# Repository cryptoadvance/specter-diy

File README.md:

# Specter-DIY

    "Cypherpunks write code. We know that someone has to write software to defend privacy, 
    and since we can't get privacy unless we all do, we're going to write it."
    A Cypherpunk's Manifesto - Eric Hughes - 9 March 1993

    ...and Cypherpunks do build their own Bitcoin Hardware Wallets.

The idea of the project is to build a hardware wallet from off-the-shelf components.
Even though we have [an extension board](./shield) that puts everything in a nice form-factor and helps you to avoid any soldering, we will continue supporting and maintaining compatibility with standard components.

We also want to keep the project flexible such that it can work on any other set of components with minimal changes. Maybe you want to make a hardware wallet on a different architecture (RISC-V?), with an audio modem as a communication channel - you should be able to do it. It should be easy to add or change functionality of Specter and we try to abstract logical modules as much as we can.

QR codes are a default way for Specter to communicate with the host. QR codes are pretty convenient and allow the user to be in control of the data transmission - every QR code has a very limited capacity and communication happens unidirectionally. And it's airgapped - you don't need to connect the wallet to the computer at any time.

For secret storage we support agnostic mode (wallet forgets all secrets when turned off), reckless mode (stores secrets in flash of the application microcontroller) and secure element integration is coming soon.

Our main focus is multisignature setup with other hardware wallets, but wallet can also work as a single signer. We try to make it compatible with Bitcoin Core where we can - PSBT for unsigned transactions, wallet descriptors for importing/exporting multisig wallets. To communicate with Bitcoin Core easier we are also working on [Specter Desktop app](https://github.com/cryptoadvance/specter-desktop) - a small python flask server talking to your Bitcoin Core node.

Most of the firmware is written in MicroPython which makes the code easy to audit and change. We use [secp256k1](https://github.com/bitcoin-core/secp256k1) library from Bitcoin Core for elliptic curve calculations and [LVGL](https://lvgl.io/) library for GUI.

## DISCLAIMER

The project has significantly matured, to the extent that the security level of Specter-DIY is now comparable to commercial hardware wallets on the market. We implemented a secure bootloader that verifies firmware upgrades, so you can be sure that only signed firmware can be uploaded to the device after initial setup. However, unlike with commercial signing devices the bootloader has to be installed manually by the user and is not set in the factory of the device vendor. Thus, pay extra attention during the initial firmware installation and make sure you verified PGP signatures and flash the firmware from a secure computer.

If something doesn't work open an issue here or ask a question in our [Telegram group](https://t.me/+VEinVSYkW5TUl5Ai).

## Documentation

All the docs are stored in the [`docs/`](./docs) folder:

- [`shopping.md`](./docs/shopping.md) explains what to buy
- [`assembly.md`](./docs/assembly.md) shows how to put everything together.
- [`quickstart.md`](./docs/quickstart.md) guides you through the initial steps how to get firmware on the board
- [`reproducible-build.md`](./docs/reproducible-build.md) describes how to build the initial firmware and upgrade files with the same hash as in the release using Docker
- [`build.md`](./docs/build.md) describes how to build the firmware and the simulator yourself
- [`security-model.md`](./docs/security-model.md) explains possible attack vectors and security model of the project
- [`SECURITY.md`](./SECURITY.md) describes how to report vulnerabilities (disclosure policy)
- [`development.md`](./docs/development.md) explains how to start developing on Specter
- [`simulator.md`](./docs/simulator.md) shows how to run a simulator on unix/macOS
- [`browser-simulator.md`](./docs/browser-simulator.md) explains the browser preview service and paired-fork setup
- [`communication.md`](./docs/communication.md) defines communication protocol with the host over QR codes and USB
- [`roadmap.md`](./docs/roadmap.md) explains what we need to implement before we can consider the wallet be ready to use with real funds.

Specter-Shield documentation and all the files are available in the [`shield/`](./shield) folder:

- [What it looks like](./shield/README.md)
- [How to print a 3d case](./shield/3dprinting.md)

Specter Shield-Lite documentation is available in the [`shield-lite/`](./shield-lite) folder:

- [Specter Shield-Lite overview](./shield-lite/readme.md)

Supported networks: Mainnet, Testnet, Regtest, Signet.

## Running tests

The unit test suite runs on the Unix simulator build. Install the required
system packages and then run the `make` target:

```
sudo apt-get update
sudo apt-get install libsdl2-dev libffi-dev pkg-config libreadline-dev libgmp-dev build-essential python3
make test
```

The build system will fetch the necessary submodules and compile the simulator
before executing the tests.

## USB communication on Linux

You may need to set up udev rules and add yourself to `dialout` group. Read more in [`udev`](./udev/README.md) folder.

## Video and screenshots

Check out [this video](https://www.youtube.com/watch?v=1H7FqG_FmCw) to get an idea how to assemble it and how it works.

Here is a [Gallery](./docs/pictures/gallery/README.md) with devices assembled by the community.

A few pictures of the UI:

### Wallet screens

### Key generation and recovery

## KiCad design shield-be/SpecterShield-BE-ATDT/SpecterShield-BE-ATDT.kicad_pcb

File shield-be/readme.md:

# Shield-BE (Budget Edition)
Work in Progress, currently untested.

The goal of this board is to provide the full functionality of the Specter Shield at a lower price.

The design parameters to enable this are:
*  4 layer PCB with largest dimension 10cm or less, min hole size 0.3mm (keeps cost down, $7 for 5pcbs)
*  All components on one side (keep fab costs down)
*  Generally target 0805 size components (make hand assembly accessible)
*  Prioritize JLCPCB basic parts, even if it means more parts taking up more space (again, to keeps costs down)
*  Can run off usb-c either with or without a battery. (Current full shield needed a battery to work, this board will not)
*  Powers the board directly from USBC when connected, rather than through the battery. (This adds some load constraints depending on what max current we assume for the USBC port. 1.5amp is probably reasonable for usb3 ports that supporting charging and will work for all USBC) Could add a resistor that is easily cut off to drop charge current down so that it will charge *and* run even off an older 1amp supply.
*  Switch mode power supply can deliver 1amp continuous with input from 3v-5v (so plenty of headroom for Specter)
*  For battery varients, can charge the lithium battery and has relevant indicator lights
*  Has power buttons, uses existing pwr_hold functionality and has power indicator when it's on.
*  Multiple varients of same design, one PCB and form factor. (Can have full shield, remove battery for shield core or remove all power for shield lite)
*  Battery level measurement on battery varient (Just using an onboard ADC, will require additional code, but will be straightforward)
*  Fully designed in kicad for portability and maintenance with FOSS tools
*  Reference case in freecad for portability and maintenance with FOSS tools

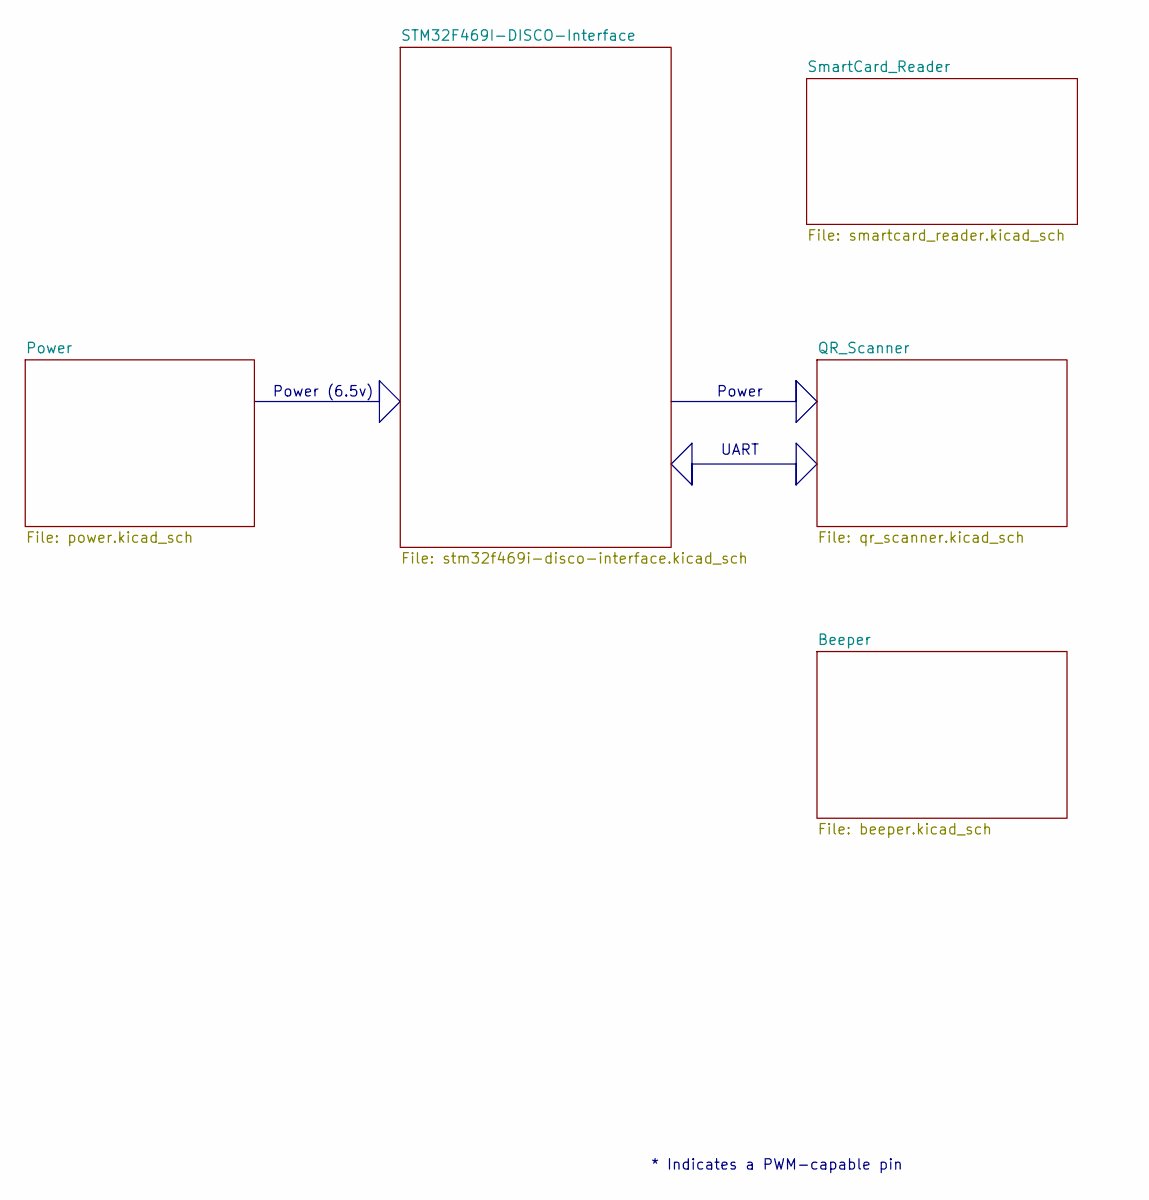
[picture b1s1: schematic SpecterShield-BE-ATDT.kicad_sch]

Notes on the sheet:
Power (6.5v)
Power
UART
* Indicates a PWM-capable pin

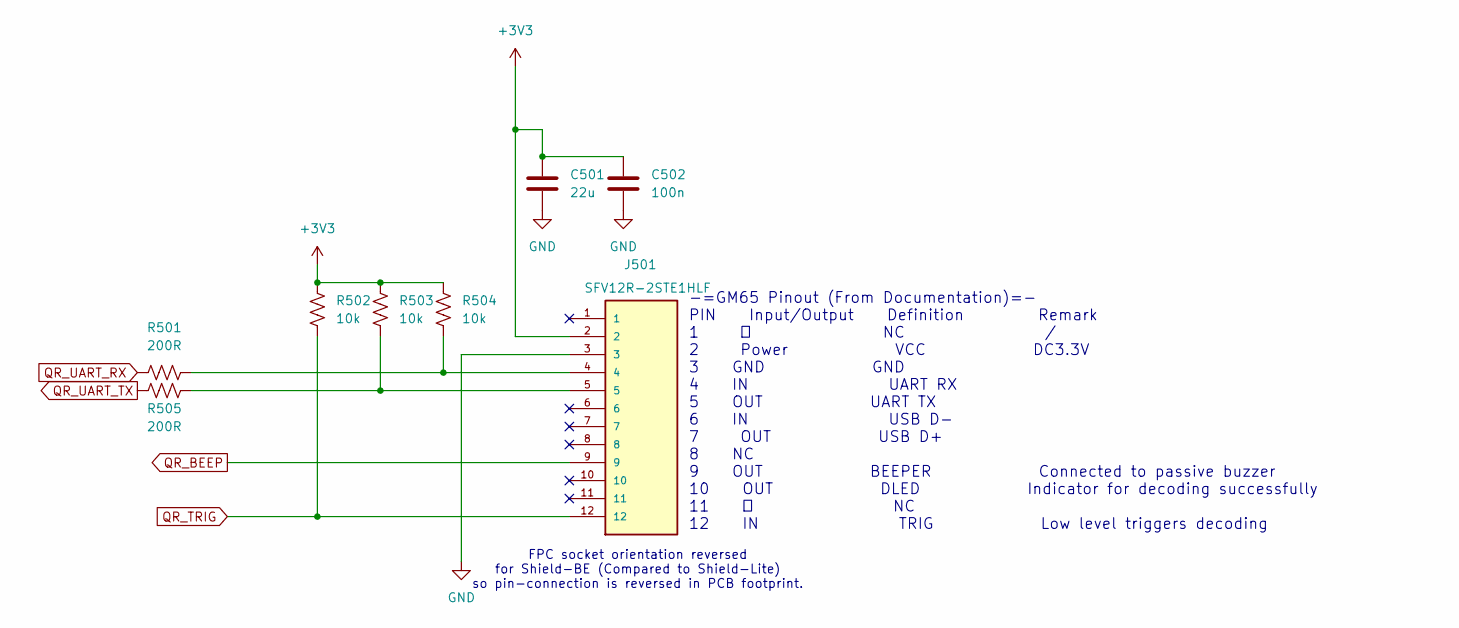
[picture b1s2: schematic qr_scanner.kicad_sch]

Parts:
C501: 22u; C_0805_2012Metric_Pad1.18x1.45mm_HandSolder; LCSC C45783
C502: 100n; C_0805_2012Metric_Pad1.18x1.45mm_HandSolder; LCSC C49678
J501: SFV12R-2STE1HLF; AMPHENOL_SFV12R-2STE1HLF_handsolder; PARTREV C; LCSC C11086
R501, R505: 200R; R_0805_2012Metric_Pad1.20x1.40mm_HandSolder; LCSC C17540
R502, R503, R504: 10k; R_0805_2012Metric_Pad1.20x1.40mm_HandSolder; LCSC C17414

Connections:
+3V3: C501.1, C502.1, J501.2, R502.1, R503.1, R504.1; also elsewhere on the board
GND: C501.2, C502.2, J501.3; also elsewhere on the board
unnamed: J501.4, R501.2, R504.2
unnamed: J501.5, R503.2, R505.2
QR_BEEP: J501.9; also elsewhere on the board
QR_TRIG: J501.12, R502.2; also elsewhere on the board
QR_UART_RX: R501.1; also elsewhere on the board
QR_UART_TX: R505.1; also elsewhere on the board

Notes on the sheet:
FPC socket orientation reversed for Shield-BE (Compared to Shield-Lite) so pin-connection is reversed in PCB footprint.
-=GM65 Pinout (From Documentation)=- PIN Input/Output Definition Remark 1 － NC / 2 Power VCC DC3.3V 3 GND GND 4 IN UART RX 5 OUT UART TX 6 IN USB D- 7 OUT USB D+ 8 NC 9 OUT BEEPER Connected to passive buzzer 10 OUT DLED Indicator for decoding successfully 11 － NC 12 IN TRIG Low level triggers decod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

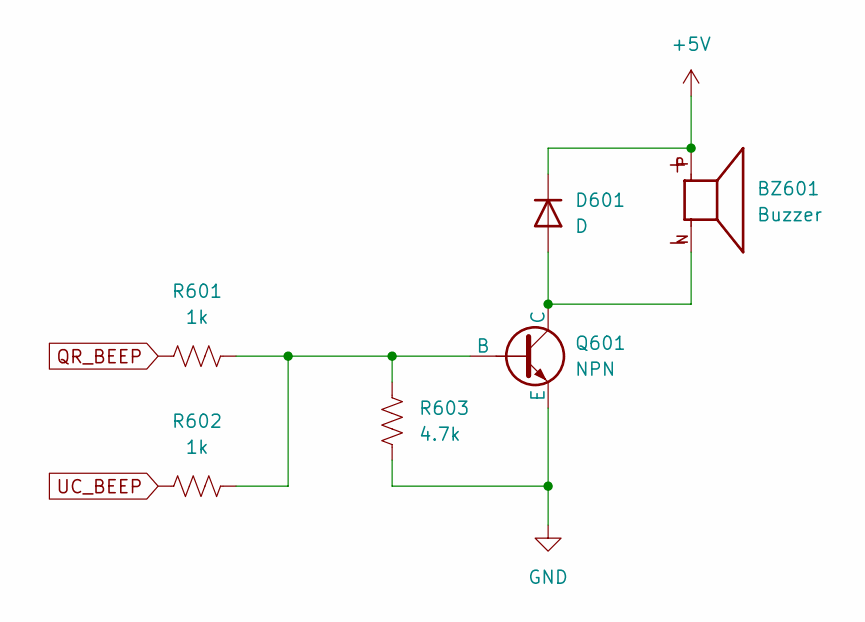
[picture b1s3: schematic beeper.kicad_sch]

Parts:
BZ601: Buzzer; XDCR_SMT-0927-S-HT-R_handsolder; PARTREV 31/03/20; LCSC C18623826
D601: D; D_SOD-123; LCSC C81598
Q601: NPN; SOT-89-3_Handsoldering; LCSC C9634
R601, R602: 1k; R_0805_2012Metric_Pad1.20x1.40mm_HandSolder; LCSC C17513
R603: 4.7k; R_0805_2012Metric_Pad1.20x1.40mm_HandSolder; LCSC C17673

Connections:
+5V: BZ601.P, D601.1 (K); also elsewhere on the board
GND: Q601.3 (E), R603.1; also elsewhere on the board
unnamed: BZ601.N, D601.2 (A), Q601.2 (C)
unnamed: Q601.1 (B), R601.2, R602.2, R603.2
QR_BEEP: R601.1; also elsewhere on the board
UC_BEEP: R602.1; also elsewhere on the board

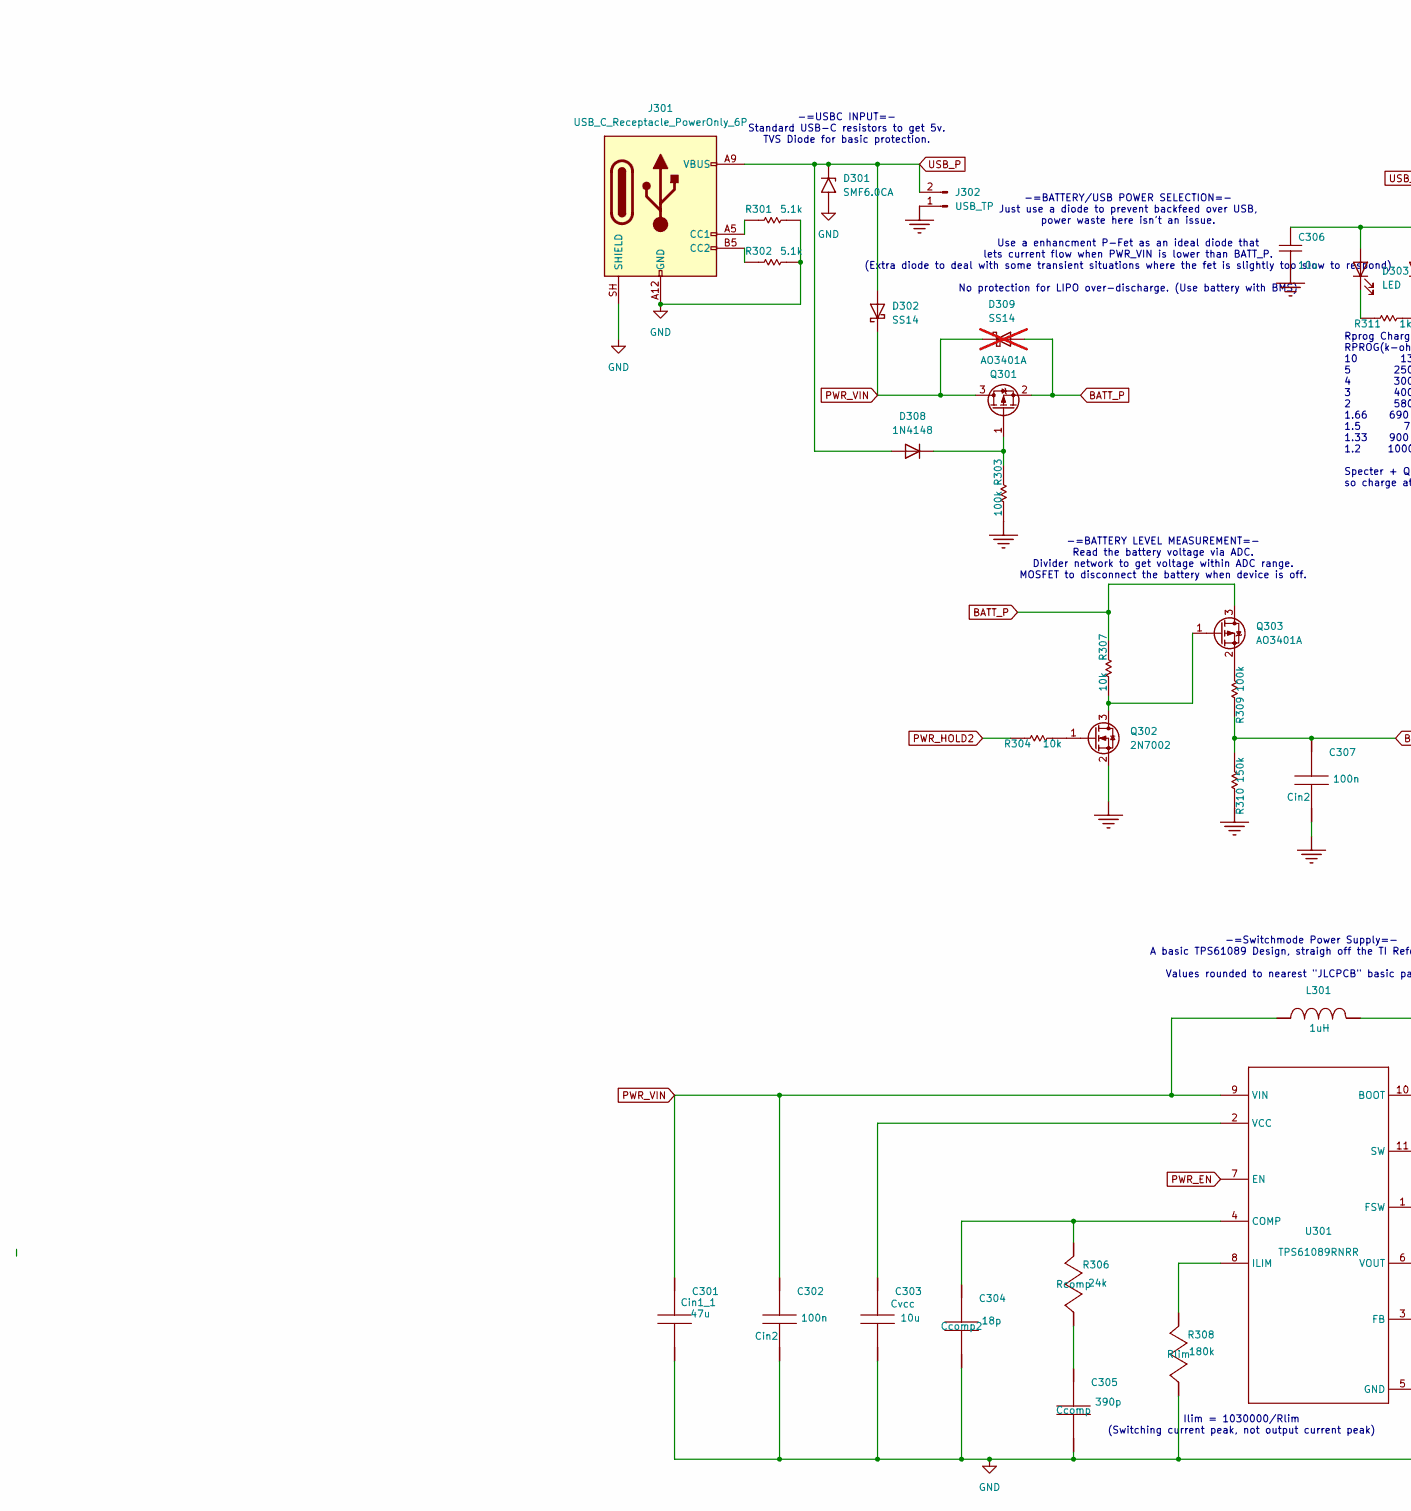
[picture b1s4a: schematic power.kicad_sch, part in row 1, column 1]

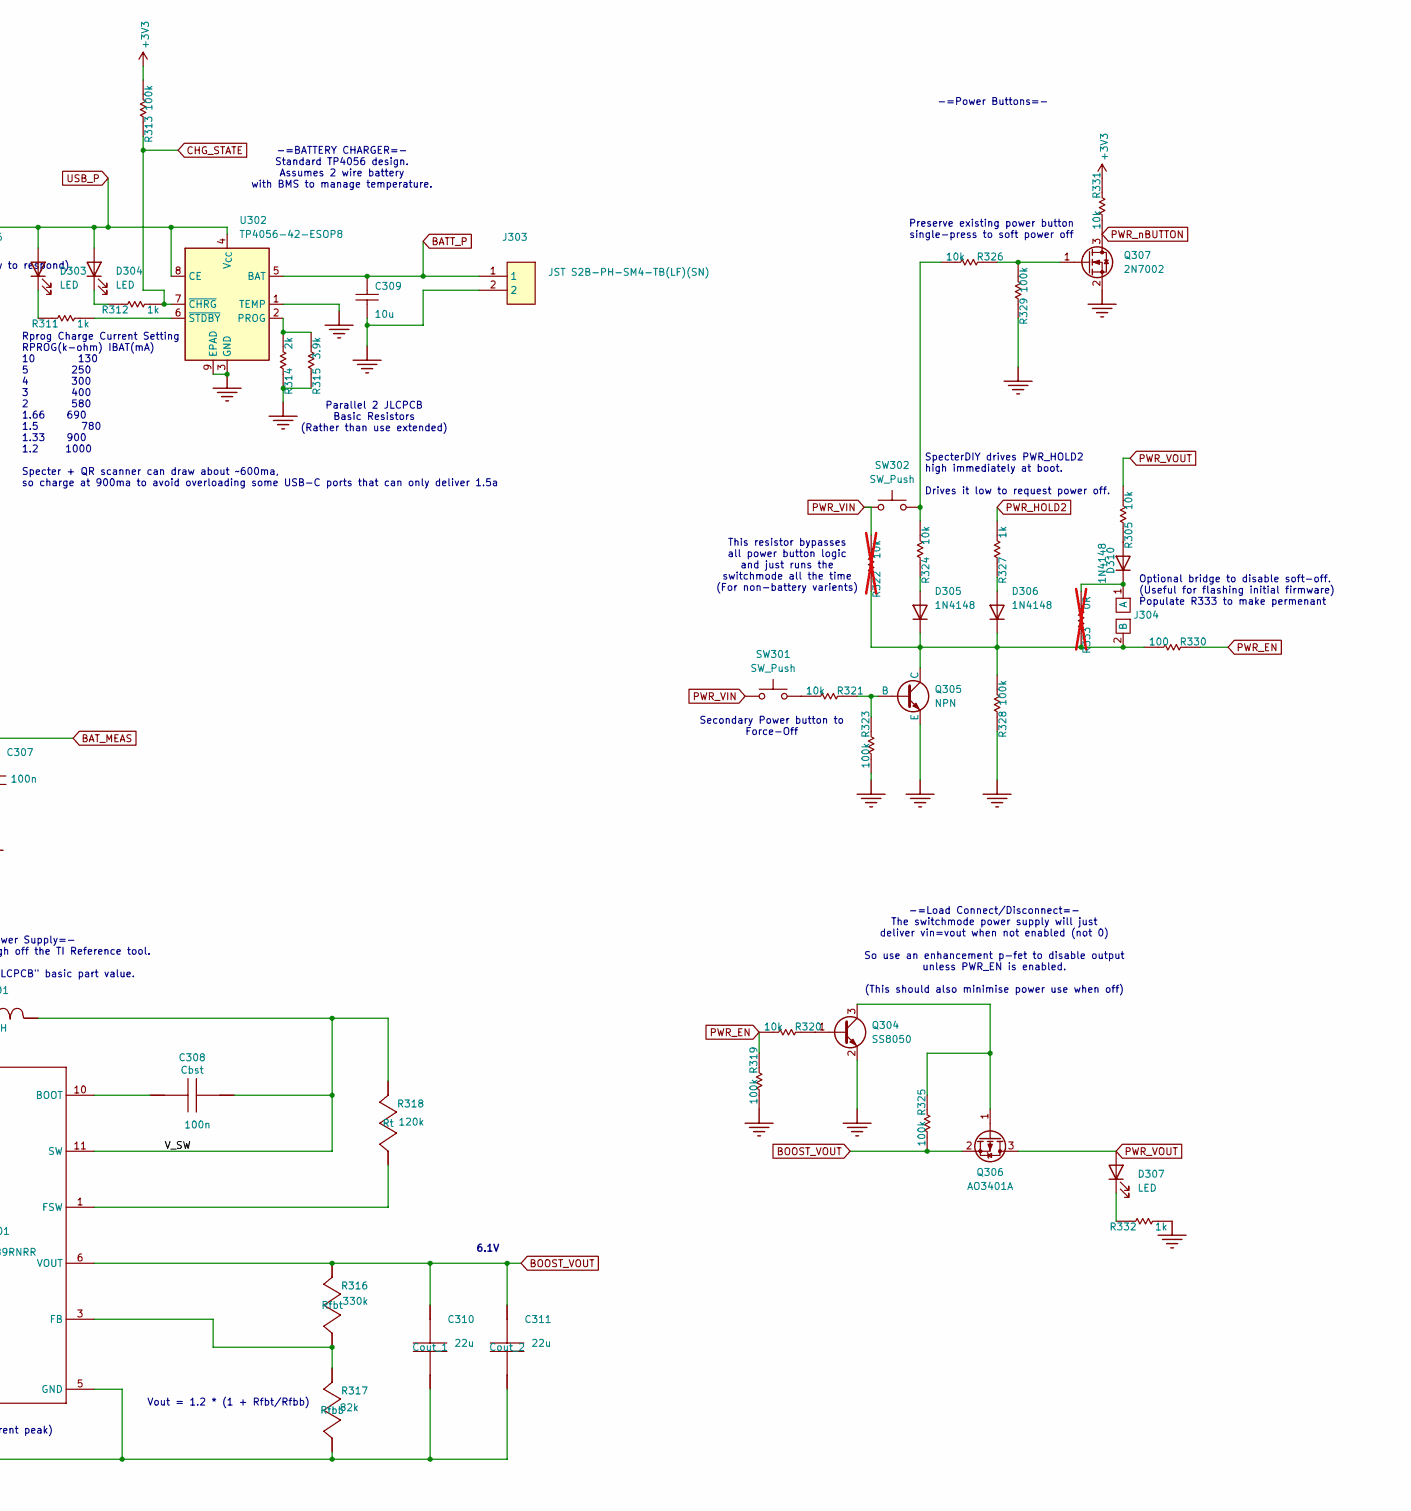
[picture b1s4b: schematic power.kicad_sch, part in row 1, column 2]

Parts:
C301: 47u; C_1206_3216Metric_Pad1.33x1.80mm_HandSolder; LCSC C96123
C302, C307, C308: 100n; C_0805_2012Metric_Pad1.18x1.45mm_HandSolder; LCSC C49678
C303: 10u; C_0805_2012Metric_Pad1.18x1.45mm_HandSolder; LCSC C15850
C304: 18p; C_0805_2012Metric_Pad1.18x1.45mm_HandSolder; LCSC C1797
C305: 390p; C_0805_2012Metric_Pad1.18x1.45mm_HandSolder; LCSC C1743
C306, C309: 10u; C_0805_2012Metric_Pad1.18x1.45mm_HandSolder; VOLTAGE RATING (DC) 50.0 V; CAPACITANCE TOLERANCE ±10%; MANUFACTURER PART NUMBER CL05B152KB5NNNC; LCSC C15850
C310, C311: 22u; C_0805_2012Metric_Pad1.18x1.45mm_HandSolder; LCSC C45783
D301: SMF6.0CA; D_SOD-123F; LCSC C2990473
D302: SS14; D_SMA; LCSC C2480
D303: LED; LED_0805_2012Metric_Pad1.15x1.40mm_HandSolder; LCSC C2296
D304: LED; LED_0805_2012Metric_Pad1.15x1.40mm_HandSolder; LCSC C84256
D305, D306, D310: 1N4148; D_SOD-323_HandSoldering; LCSC C2128
D307: LED; LED_0805_2012Metric_Pad1.15x1.40mm_HandSolder; LCSC C2297
D308: 1N4148; D_SOD-323
D309: SS14; D_SMA; LCSC C2480; not fitted
J301: USB_C_Receptacle_PowerOnly_6P; USB_C_Receptacle_HRO_TYPE-C-31-M-17; LCSC C668623
J302: USB_TP; PinHeader_1x02_P2.54mm_Vertical
J303: JST S2B-PH-SM4-TB(LF)(SN); JST_PH_S2B-PH-SM4-TB_1x02-1MP_P2.00mm_Horizontal; LCSC C295747
J304: BridgePads
L301: 1uH; L_1210_3225Metric_Pad1.42x2.65mm_HandSolder; LCSC C3002557
Q301, Q303, Q306: AO3401A; SOT-23; LCSC C15127
Q302, Q307: 2N7002; SOT-23; LCSC C8545
Q304: SS8050; SOT-23; LCSC C2150
Q305: NPN; SOT-89-3_Handsoldering; LCSC C9634
R301, R302: 5.1k; R_0805_2012Metric_Pad1.20x1.40mm_HandSolder; POWER RATING 0.0625 W; RESISTANCE TOLERANCE ±1%; MANUFACTURER PART NUMBER RC0402FR-07200RL; LCSC C27834
R303, R309, R313, R319, R323, R325, R328, R329: 100k; R_0805_2012Metric_Pad1.20x1.40mm_HandSolder; POWER RATING 0.063 W; RESISTANCE TOLERANCE ±1%; MANUFACTURER PART NUMBER RC0402FR-07120KL; LCSC C149504
R304, R305, R307, R320, R321, R324, R326, R331: 10k; R_0805_2012Metric_Pad1.20x1.40mm_HandSolder; POWER RATING 0.063 W; RESISTANCE TOLERANCE ±1%; MANUFACTURER PART NUMBER RC0402FR-07120KL; LCSC C17414
R306: 24k; R_0805_2012Metric_Pad1.20x1.40mm_HandSolder; LCSC C17575
R308: 180k; R_0805_2012Metric_Pad1.20x1.40mm_HandSolder; LCSC C17501
R310: 150k; R_0805_2012Metric_Pad1.20x1.40mm_HandSolder; POWER RATING 0.063 W; RESISTANCE TOLERANCE ±1%; MANUFACTURER PART NUMBER RC0402FR-07120KL; LCSC C17470
R311, R312, R327, R332: 1k; R_0805_2012Metric_Pad1.20x1.40mm_HandSolder; POWER RATING 0.063 W; RESISTANCE TOLERANCE ±1%; MANUFACTURER PART NUMBER RC0402FR-07120KL; LCSC C17513
R314: 2k; R_0805_2012Metric_Pad1.20x1.40mm_HandSolder; POWER RATING 0.063 W; RESISTANCE TOLERANCE ±1%; MANUFACTURER PART NUMBER RC0402FR-07120KL; LCSC C17604
R315: 3.9k; R_0805_2012Metric_Pad1.20x1.40mm_HandSolder; POWER RATING 0.063 W; RESISTANCE TOLERANCE ±1%; MANUFACTURER PART NUMBER RC0402FR-07120KL; LCSC C17614
R316: 330k; R_0805_2012Metric_Pad1.20x1.40mm_HandSolder; LCSC C23137
R317: 82k; R_0805_2012Metric_Pad1.20x1.40mm_HandSolder; LCSC C17840
R318: 120k; R_0805_2012Metric_Pad1.20x1.40mm_HandSolder; LCSC C25808
R322: 10k; R_0805_2012Metric_Pad1.20x1.40mm_HandSolder; POWER RATING 0.063 W; RESISTANCE TOLERANCE ±1%; MANUFACTURER PART NUMBER RC0402FR-07120KL; LCSC C17414; not fitted
R330: 100; R_0805_2012Metric_Pad1.20x1.40mm_HandSolder; POWER RATING 0.063 W; RESISTANCE TOLERANCE ±1%; MANUFACTURER PART NUMBER RC0402FR-07120KL; LCSC C1015
R333: 0R; R_0805_2012Metric_Pad1.20x1.40mm_HandSolder; POWER RATING 0.063 W; RESISTANCE TOLERANCE ±1%; MANUFACTURER PART NUMBER RC0402FR-07120KL; LCSC C17414; not fitted
SW301, SW302: SW_Push; SW_SPST_SKQG_WithStem; LCSC C318884
U301: TPS61089RNRR; Texas_VQFN-RNR0011A-11; MANUFACTURER PART NUMBER TPS61089RNRR; LCSC C165129
U302: TP4056-42-ESOP8; SOIC-8-1EP_3.9x4.9mm_P1.27mm_EP2.41x3.3mm_ThermalVias; LCSC C16581

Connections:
+3V3: R313.2, R331.1; also elsewhere on the board
/Power/V_SW: C308.2, L301.2, R318.1, U301.11 (SW)
BATT_P: C309.2, D309.2 (A), J303.1, Q301.2 (S), Q303.3 (D), R307.1, U302.5 (BAT)
BAT_MEAS: C307.1, R309.1, R310.2; also elsewhere on the board
BOOST_VOUT: C310.1, C311.1, Q306.2 (S), R316.1, R325.2, U301.6 (VOUT)
CHG_STATE: R312.2, R313.1, U302.7 (~CHRG); also elsewhere on the board
GND: C301.2, C302.2, C303.2, C304.2, C305.2, C306.1, C307.2, C309.1, C310.2, C311.2, D301.2 (A2), J301.A12 (GND), J301.B12 (GND), J301.SH (SHIELD), J302.1, J303.2, Q302.2 (S), Q304.2 (E), Q305.3 (E), Q307.2 (S), R301.2, R302.2, R303.2, R308.2, R310.1, R314.1, R315.1, R317.2, R319.2, R323.2, R328.1, R329.1, R332.2, U301.5 (GND), U302.1 (TEMP), U302.3 (GND), U302.9 (EPAD); also elsewhere on the board
unnamed: C305.1, R306.2
unnamed: D303.1 (K), R311.1
unnamed: D304.1 (K), R312.1
unnamed: D305.2 (A), R324.1
unnamed: D305.1 (K), D306.1 (K), J304.2 (B), Q305.2 (C), R322.1, R328.2, R330.2, R333.1
unnamed: D306.2 (A), R327.1
unnamed: D307.1 (K), R332.1
unnamed: D308.1 (K), Q301.1 (G), R303.1
unnamed: D310.2 (A), R305.1
unnamed: D310.1 (K), J304.1 (A), R333.2
unnamed: J301.A5 (CC1), R301.1
unnamed: J301.B5 (CC2), R302.1
unnamed: Q302.3 (D), Q303.1 (G), R307.2
unnamed: Q302.1 (G), R304.2
unnamed: Q303.2 (S), R309.2
unnamed: Q304.1 (B), R320.1
unnamed: Q304.3 (C), Q306.1 (G), R325.1
unnamed: Q305.1 (B), R321.1, R323.1
unnamed: Q307.1 (G), R326.1, R329.2
unnamed: R321.2, SW301.2
unnamed: R324.2, R326.2, SW302.2
unnamed: C308.1, U301.10 (BOOT)
unnamed: C304.1, R306.1, U301.4 (COMP)
unnamed: R316.2, R317.1, U301.3 (FB)
unnamed: R318.2, U301.1 (FSW)
unnamed: R308.1, U301.8 (ILIM)
unnamed: C303.1, U301.2 (VCC)
unnamed: R314.2, R315.2, U302.2 (PROG)
unnamed: R311.2, U302.6 (~STDBY)
PWR_EN: R319.1, R320.2, R330.1, U301.7 (EN)
PWR_HOLD2: R304.1, R327.2; also elsewhere on the board
PWR_VIN: C301.1, C302.1, D302.1 (K), D309.1 (K), L301.1, Q301.3 (D), R322.2, SW301.1, SW302.1, U301.9 (VIN)
PWR_VOUT: D307.2 (A), Q306.3 (D), R305.2; also elsewhere on the board
PWR_nBUTTON: Q307.3 (D), R331.2; also elsewhere on the board
USB_P: C306.2, D301.1 (A1), D302.2 (A), D303.2 (A), D304.2 (A), D308.2 (A), J301.A9 (VBUS), J301.B9 (VBUS), J302.2, U302.4 (V_{CC}), U302.8 (CE)

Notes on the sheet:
6.1V
Ilim = 1030000/Rlim (Switching current peak, not output current peak)
-=BATTERY LEVEL MEASUREMENT=- Read the battery voltage via ADC. Divider network to get voltage within ADC range. MOSFET to disconnect the battery when device is off.
This resistor bypasses all power button logic and just runs the switchmode all the time (For non-battery varients)
-=Load Connect/Disconnect=- The switchmode power supply will just deliver vin=vout when not enabled (not 0) So use an enhancement p-fet to disable output unless PWR_EN is enabled. (This should also minimise power use when off)
Vout = 1.2 * (1 + Rfbt/Rfbb)
-=BATTERY CHARGER=- Standard TP4056 design. Assumes 2 wire battery with BMS to manage temperature.
-=Power Buttons=-
-=USBC INPUT=- Standard USB-C resistors to get 5v. TVS Diode for basic protection.
-=BATTERY/USB POWER SELECTION=- Just use a diode to prevent backfeed over USB, power waste here isn't an issue. Use a enhancment P-Fet as an ideal diode that lets current flow when PWR_VIN is lower than BATT_P. (Extra diode to deal with some transient situations where the fet is slightly too slow t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
Optional bridge to disable soft-off. (Useful for flashing initial firmware) Populate R333 to make permenant
Secondary Power button to Force-Off
Parallel 2 JLCPCB Basic Resistors (Rather than use extended)
SpecterDIY drives PWR_HOLD2 high immediately at boot. Drives it low to request power off.
-=Switchmode Power Supply=- A basic TPS61089 Design, straigh off the TI Reference tool. Values rounded to nearest "JLCPCB" basic part value.
Rprog Charge Current Setting RPROG(k-ohm) IBAT(mA) 10 130 5 250 4 300 3 400 2 580 1.66 690 1.5 780 1.33 900 1.2 1000 Specter + QR scanner can draw about ~600ma, so charge at 900ma to avoid overloading some USB-C ports that can only deliver 1.5a
Preserve existing power button single-press to soft power off

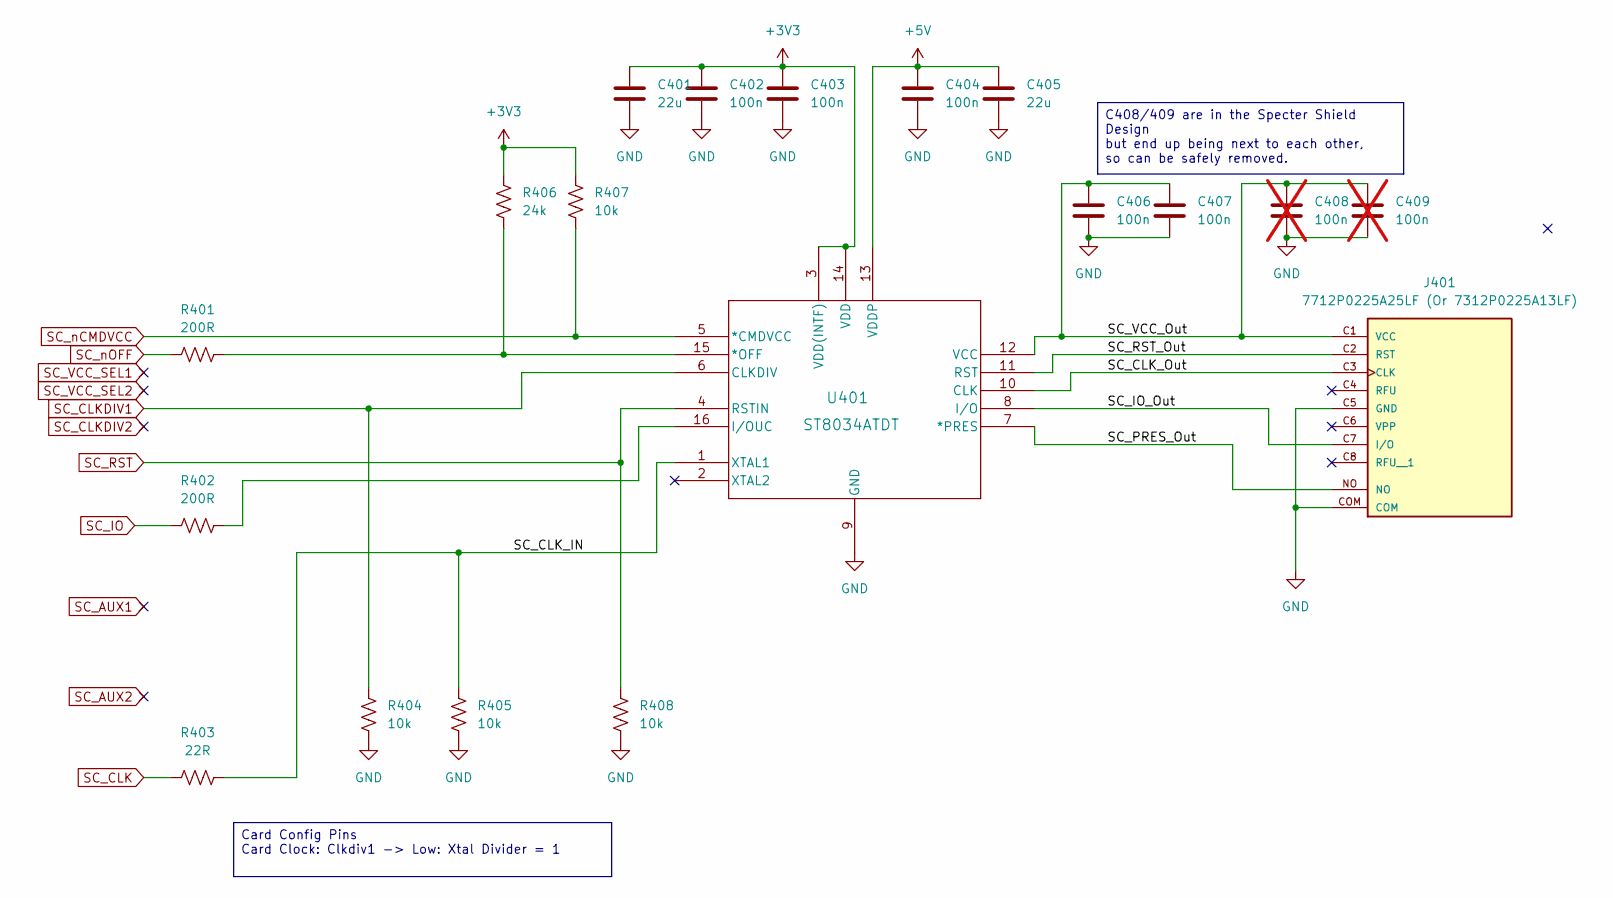
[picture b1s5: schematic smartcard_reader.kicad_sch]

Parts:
C401, C405: 22u; C_0805_2012Metric_Pad1.18x1.45mm_HandSolder; LCSC C45783
C402, C403, C404, C406, C407: 100n; C_0805_2012Metric_Pad1.18x1.45mm_HandSolder; LCSC C49678
C408, C409: 100n; C_0805_2012Metric_Pad1.18x1.45mm_HandSolder; not fitted
J401: 7712P0225A25LF (Or 7312P0225A13LF); AMPHENOL_7312P0225A13LF_smrt2_combo_handsolder; PARTREV L; LCSC C599034
R401, R402: 200R; R_0805_2012Metric_Pad1.20x1.40mm_HandSolder; LCSC C17540
R403: 22R; R_0805_2012Metric_Pad1.20x1.40mm_HandSolder; LCSC C17561
R404, R405, R407, R408: 10k; R_0805_2012Metric_Pad1.20x1.40mm_HandSolder; LCSC C17414
R406: 24k; R_0805_2012Metric_Pad1.20x1.40mm_HandSolder; LCSC C17575
U401: ST8034ATDT; SO-16_STM_handsolder; LCSC C2674140

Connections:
+3V3: C401.1, C402.1, C403.1, R406.1, R407.1, U401.3 (VDD(INTF)), U401.14 (VDD); also elsewhere on the board
+5V: C404.1, C405.1, U401.13 (VDDP); also elsewhere on the board
/SmartCard_Reader/SC_CLK_IN: R403.2, R405.1, U401.1 (XTAL1)
/SmartCard_Reader/SC_CLK_Out: J401.C3 (CLK), U401.10 (CLK)
/SmartCard_Reader/SC_IO_Out: J401.C7 (I/O), U401.8 (I/O)
/SmartCard_Reader/SC_PRES_Out: J401.NO, U401.7 (*PRES)
/SmartCard_Reader/SC_RST_Out: J401.C2 (RST), U401.11 (RST)
/SmartCard_Reader/SC_VCC_Out: C406.1, C407.1, C408.1, C409.1, J401.C1 (VCC), U401.12 (VCC)
GND: C401.2, C402.2, C403.2, C404.2, C405.2, C406.2, C407.2, C408.2, C409.2, J401.C5 (GND), J401.COM, R404.1, R405.2, R408.2, U401.9 (GND); also elsewhere on the board
unnamed: R401.2, R406.2, U401.15 (*OFF)
unnamed: R402.2, U401.16 (I/OUC)
SC_CLK: R403.1; also elsewhere on the board
SC_CLKDIV1: R404.2, U401.6 (CLKDIV); also elsewhere on the board
SC_IO: R402.1; also elsewhere on the board
SC_RST: R408.1, U401.4 (RSTIN); also elsewhere on the board
SC_nCMDVCC: R407.2, U401.5 (*CMDVCC); also elsewhere on the board
SC_nOFF: R401.1; also elsewhere on the board

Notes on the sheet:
C408/409 are in the Specter Shield Design but end up being next to each other, so can be safely removed.
Card Config Pins Card Clock: Clkdiv1 -> Low: Xtal Divider = 1

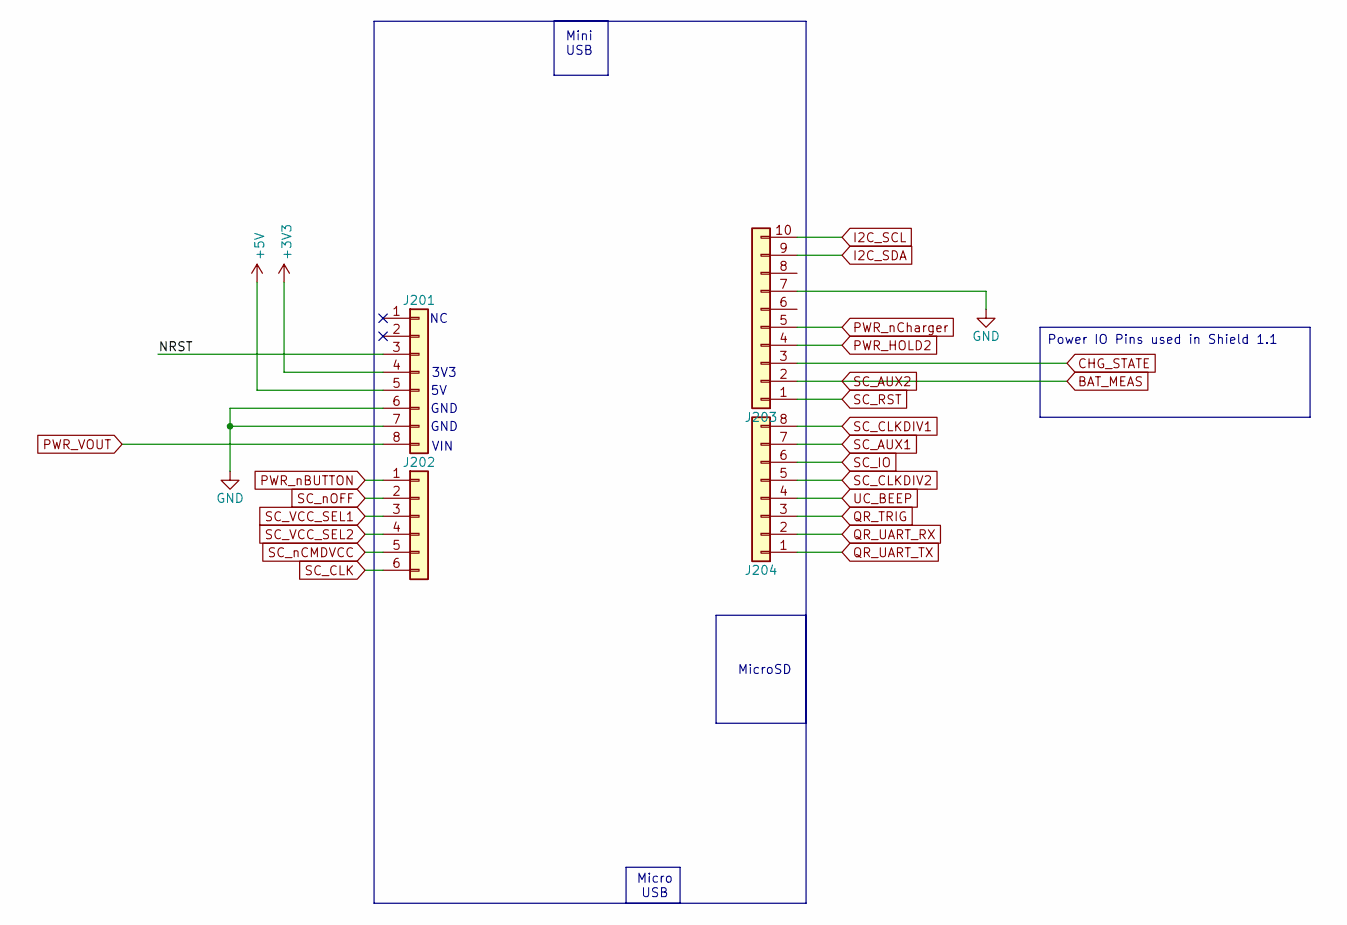
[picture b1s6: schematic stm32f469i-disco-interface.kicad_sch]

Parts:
J201, J204: M20-8770842; PinHeader_1x08_P2.54mm_Vertical_SMD_Pin1Right_handsolder; Mouser_Ref 855-M20-8770842
J202: M20-8770642; PinHeader_1x06_P2.54mm_Vertical_SMD_Pin1Right_handsolder; Mouser_Ref 855-M20-8770642
J203: M20-8771042; PinHeader_1x10_P2.54mm_Vertical_SMD_Pin1Right_handsolder; Mouser_Ref 855-M20-8771042

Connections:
+3V3: J201.4; also elsewhere on the board
+5V: J201.5; also elsewhere on the board
/STM32F469I-DISCO-Interface/NRST: J201.3
BAT_MEAS: J203.2; also elsewhere on the board
CHG_STATE: J203.3; also elsewhere on the board
GND: J201.6, J201.7, J203.7; also elsewhere on the board
I2C_SCL: J203.10
I2C_SDA: J203.9
PWR_HOLD2: J203.4; also elsewhere on the board
PWR_VOUT: J201.8; also elsewhere on the board
PWR_nBUTTON: J202.1; also elsewhere on the board
PWR_nCharger: J203.5
QR_TRIG: J204.3; also elsewhere on the board
QR_UART_RX: J204.2; also elsewhere on the board
QR_UART_TX: J204.1; also elsewhere on the board
SC_AUX1: J204.7
SC_AUX1_1: J204.7
SC_CLK: J202.6; also elsewhere on the board
SC_CLKDIV1: J204.8; also elsewhere on the board
SC_CLKDIV2: J204.5
SC_CLKDIV2_1: J204.5
SC_IO: J204.6; also elsewhere on the board
SC_RST: J203.1; also elsewhere on the board
SC_VCC_SEL1: J202.3
SC_VCC_SEL1_1: J202.3
SC_VCC_SEL2: J202.4
SC_VCC_SEL2_1: J202.4
SC_nCMDVCC: J202.5; also elsewhere on the board
SC_nOFF: J202.2; also elsewhere on the board
UC_BEEP: J204.4; also elsewhere on the board

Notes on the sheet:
GND
3V3
VIN
Micro USB
MicroSD
Mini USB
Power IO Pins used in Shield 1.1

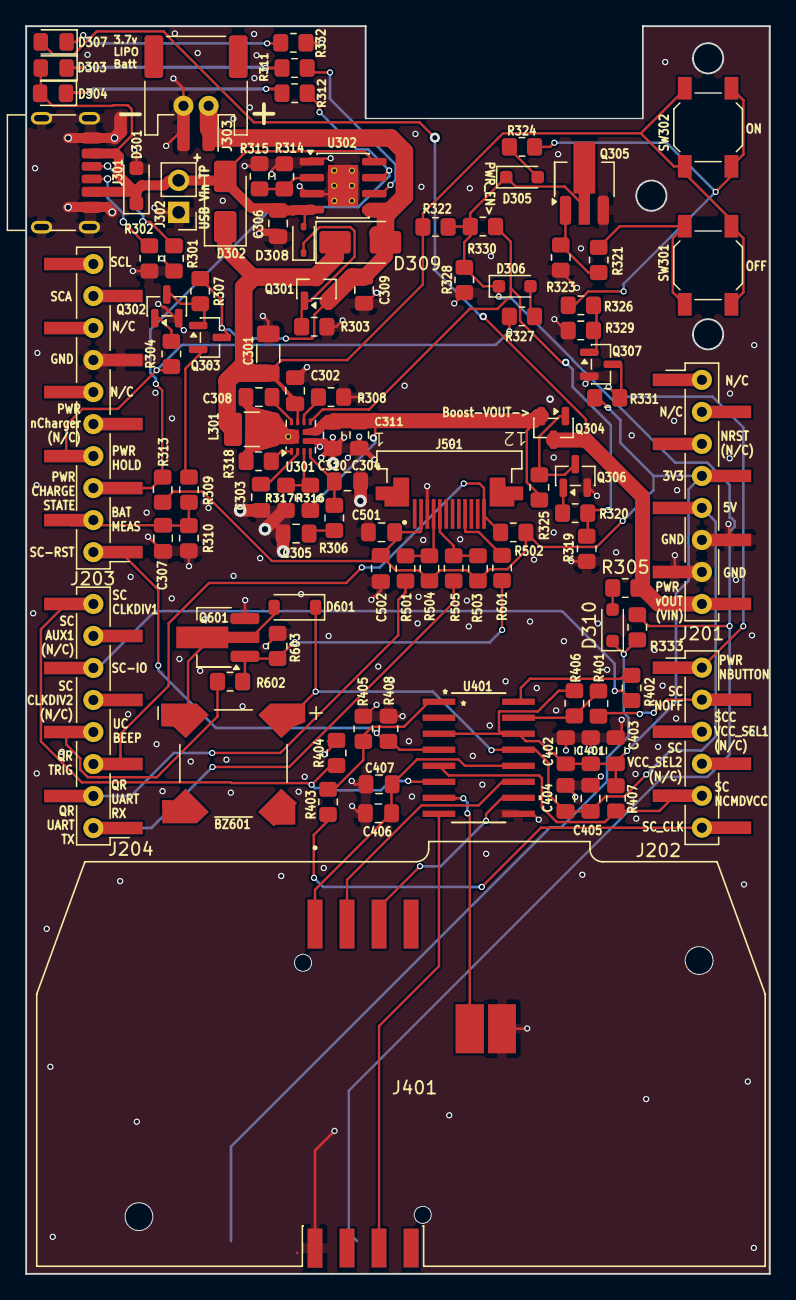
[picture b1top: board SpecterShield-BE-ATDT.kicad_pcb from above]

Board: 4 copper layers, 59.0 x 99.0 mm, 105 parts (1 on the bottom side), 66 nets.

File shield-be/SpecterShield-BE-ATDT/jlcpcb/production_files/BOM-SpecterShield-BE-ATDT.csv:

Comment,Designator,Footprint,LCSC,Quantity
100,R330,R_0805_2012Metric_Pad1.20x1.40mm_HandSolder,C1015,1
100k,"R303,R309,R313,R319,R323,R325,R328,R329",R_0805_2012Metric_Pad1.20x1.40mm_HandSolder,C149504,8
100n,"C302,C307,C308,C402,C403,C404,C406,C407,C502",C_0805_2012Metric_Pad1.18x1.45mm_HandSolder,C49678,9
10k,"R304,R305,R307,R320,R321,R324,R326,R331,R404,R405,R407,R408,R502,R503,R504",R_0805_2012Metric_Pad1.20x1.40mm_HandSolder,C17414,15
10u,"C303,C306,C309",C_0805_2012Metric_Pad1.18x1.45mm_HandSolder,C15850,3
120k,R318,R_0805_2012Metric_Pad1.20x1.40mm_HandSolder,C25808,1
150k,R310,R_0805_2012Metric_Pad1.20x1.40mm_HandSolder,C17470,1
180k,R308,R_0805_2012Metric_Pad1.20x1.40mm_HandSolder,C17501,1
18p,C304,C_0805_2012Metric_Pad1.18x1.45mm_HandSolder,C1797,1
1N4148,"D305,D306,D308,D310",D_SOD-323_HandSoldering,C2128,4
1k,"R311,R312,R327,R332,R601,R602",R_0805_2012Metric_Pad1.20x1.40mm_HandSolder,C17513,6
1uH,L301,L_1210_3225Metric_Pad1.42x2.65mm_HandSolder,C3002557,1
200R,"R401,R402,R501,R505",R_0805_2012Metric_Pad1.20x1.40mm_HandSolder,C17540,4
22R,R403,R_0805_2012Metric_Pad1.20x1.40mm_HandSolder,C17561,1
22u,"C310,C311,C401,C405,C501",C_0805_2012Metric_Pad1.18x1.45mm_HandSolder,C45783,5
24k,"R306,R406",R_0805_2012Metric_Pad1.20x1.40mm_HandSolder,C17575,2
2N7002,"Q302,Q307",SOT-23,C8545,2
2k,R314,R_0805_2012Metric_Pad1.20x1.40mm_HandSolder,C17604,1
3.9k,R315,R_0805_2012Metric_Pad1.20x1.40mm_HandSolder,C17614,1
330k,R316,R_0805_2012Metric_Pad1.20x1.40mm_HandSolder,C23137,1
390p,C305,C_0805_2012Metric_Pad1.18x1.45mm_HandSolder,C1743,1
4.7k,R603,R_0805_2012Metric_Pad1.20x1.40mm_HandSolder,C17673,1
47u,C301,C_1206_3216Metric_Pad1.33x1.80mm_HandSolder,C96123,1
5.1k,"R301,R302",R_0805_2012Metric_Pad1.20x1.40mm_HandSolder,C27834,2
7712P0225A25LF (Or 7312P0225A13LF),J401,AMPHENOL_7312P0225A13LF_smrt2_combo_handsolder,C599034,1
82k,R317,R_0805_2012Metric_Pad1.20x1.40mm_HandSolder,C17840,1
AO3401A,"Q301,Q303,Q306",SOT-23,C15127,3
Buzzer,BZ601,XDCR_SMT-0927-S-HT-R_handsolder,C18623826,1
D,D601,D_SOD-123,C81598,1
JST S2B-PH-SM4-TB(LF)(SN),J303,JST_PH_S2B-PH-SM4-TB_1x02-1MP_P2.00mm_Horizontal,C295747,1
LED,D303,LED_0805_2012Metric_Pad1.15x1.40mm_HandSolder,C2296,1
LED,D307,LED_0805_2012Metric_Pad1.15x1.40mm_HandSolder,C2297,1
LED,D304,LED_0805_2012Metric_Pad1.15x1.40mm_HandSolder,C84256,1
M20-8770642,J202,PinHeader_1x06_P2.54mm_Vertical_SMD_Pin1Right_handsolder_reverse,C2883763,1
M20-8770842,"J201,J204",PinHeader_1x08_P2.54mm_Vertical_SMD_Pin1Right_handsolder_reverse,C2883765,2
M20-8771042,J203,PinHeader_1x10_P2.54mm_Vertical_SMD_Pin1Right_handsolder_reversed,C2883767,1
NPN,"Q305,Q601",SOT-89-3_Handsoldering,C9634,2
SFV12R-2STE1HLF,J501,AMPHENOL_SFV12R-2STE1HLF_handsolder,C11086,1
SMF6.0CA,D301,D_SOD-123F,C2990473,1
SS14,D302,D_SMA,C2480,1
SS8050,Q304,SOT-23,C2150,1
ST8034ATDT,U401,SO-16_STM_handsolder,C2674140,1
SW_Push,"SW301,SW302",SW_SPST_SKQG_WithStem,C318884,2
TP4056-42-ESOP8,U302,SOIC-8-1EP_3.9x4.9mm_P1.27mm_EP2.41x3.3mm_ThermalVias,C16581,1
TPS61089RNRR,U301,Texas_VQFN-RNR0011A-11,C165129,1
USB_C_Receptacle_PowerOnly_6P,J301,USB_C_Receptacle_HRO_TYPE-C-31-M-17,C668623,1
~,J304,BridgePads,,1
